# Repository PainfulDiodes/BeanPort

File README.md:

# BeanPort

Raspberry Pi Pico firmware providing a USB bridge for retrocomputers.

See also: [PainfulDiodes Blog: BeanPort](https://painfuldiodes.wordpress.com/category/beanport/)

Most homebrew retrocomputing designs provide a UART interface and use an FTDI UART-to-USB adapter to connect to a modern host computer. This means dealing with baud rates, and either fixing the CPU clock to a UART-friendly rate, or having a separate clock for the UART.

BeanPort provides an alternative solution: using a Pico, with its own USB interface, to replace the UART and FTDI adapter on the retro target.

The FTDI UM245R USB-to-parallel-FIFO module provides a similar function, but the Pico is lower cost and more readily available. It also has further potential through the Pico's SDK and additional capabilities.

The Pico's GPIOs present a two-register, 8-bit parallel interface to the target system's bus.

The Pico's USB appears as a standard CDC-ACM USB device (Abstract Control Model Communications Device Class) which the host computer recognises with a standard driver to deliver a VCP (Virtual COM Port) — on macOS: `/dev/cu.usbmodemXXXX`

USB CDC is provided by [TinyUSB](https://github.com/hathach/tinyusb) within the Pico SDK.

(By comparison, the UM245R communicates with an FTDI-specific driver on the host system, which also typically presents the device to the host as a VCP.)

Bytes flow transparently with buffering in both directions, so you can run a virtual terminal — PuTTY, screen, minicom, CoolTerm etc. — on the host computer to access the retrocomputer.

## Target Interface

BeanPort provides two 8-bit registers, distinguished by a Register Select (RS) input (which will typically be mapped to the target's A0):

| RS/A0 | Name   | Access     | Meaning                                                                                    |
|-------|--------|------------|--------------------------------------------------------------------------------------------|
| 0     | STATUS | read-only  | bit 0 = read-available, bit 1 = write-ready (matches the 6850 ACIA's RDRF/TDRE convention) |
| 1     | DATA   | read/write | write = byte to send to the host; read = byte received from the host                       |

The target will also provide EN# (enable), and R/W# - high for a read and low for a write, 6502-style. For a Z80 target: WR# would map directly to R/W#.

Reading data when none is available returns `0x00`.

## Bus Timing

The bus is handled by a PIO state machine. It responds a fixed number of PIO cycles after EN# falls - at 125MHz on an RP2040:

- **Read**: BeanPort drives the data bus as soon as EN# falls, but the byte is only valid about 90ns later for DATA, and about 145ns later for STATUS. The bus is released when EN# rises
- **Write**: BeanPort samples the data bus about 95ns after EN# falls, not when EN# rises
- RS (A0) and R/W# must be valid when EN# falls, and held until it rises

The figures above are estimated from the PIO cycle counts, and don't include level shifter delays.

Tests succeeded with:

- 10MHz Z80 - as a port-addressed device (IORQ#)
- 65C02 at up to 2.67MHz with a symmetrical clock - as a memory-mapped device, with EN# gated on PHI2

## Hardware

BeanPort should work with all current Raspberry Pi Pico variants: Pico (RP2040) and Pico 2 (RP2350), and wireless (`W`) versions. To date, it has only been tested with a non-wireless RP2040.

The following example schematic shows the designations of the Pico pins, and has 3.3V level shifters whose outputs are in spec for TTL-level inputs - 74HCT/LS logic, the W65C22N VIA and the Z80 - but I think not CMOS-level inputs such as 74HC logic. The connectors indicate how I intend to connect the BeanPort to my [Bean65](https://github.com/PainfulDiodes/bean65) board which has a W65C22N VIA "slow bus" - using the same connector layout as [Garth Wilson's 6502 design](https://wilsonminesco.com/6502primer/potpourri.html):

[kicad/beanport.pdf](kicad/beanport.pdf)

Breadboard prototype connected to a Z80 bus, with the addition of a '138 for port address decoding:

## Building and flashing

The repo's uf2 files can be transferred to Pico with standard BOOTSEL. Binary location: `build/<target>/bin/beanport.uf2`

Firmware can be built from source — see Pico documentation for build toolchain / process.

Each board gets its own build directory, e.g. `build/pico2_w/`

## License

MIT — see [LICENSE](LICENSE).

## Links

- [BeanZee](https://github.com/PainfulDiodes/BeanZee)
- [Bean65](https://github.com/PainfulDiodes/bean65)
- [BeanBoard](https://github.com/PainfulDiodes/BeanBoard)
- [PainfulDiodes Blog: BeanPort](https://painfuldiodes.wordpress.com/category/beanport/)

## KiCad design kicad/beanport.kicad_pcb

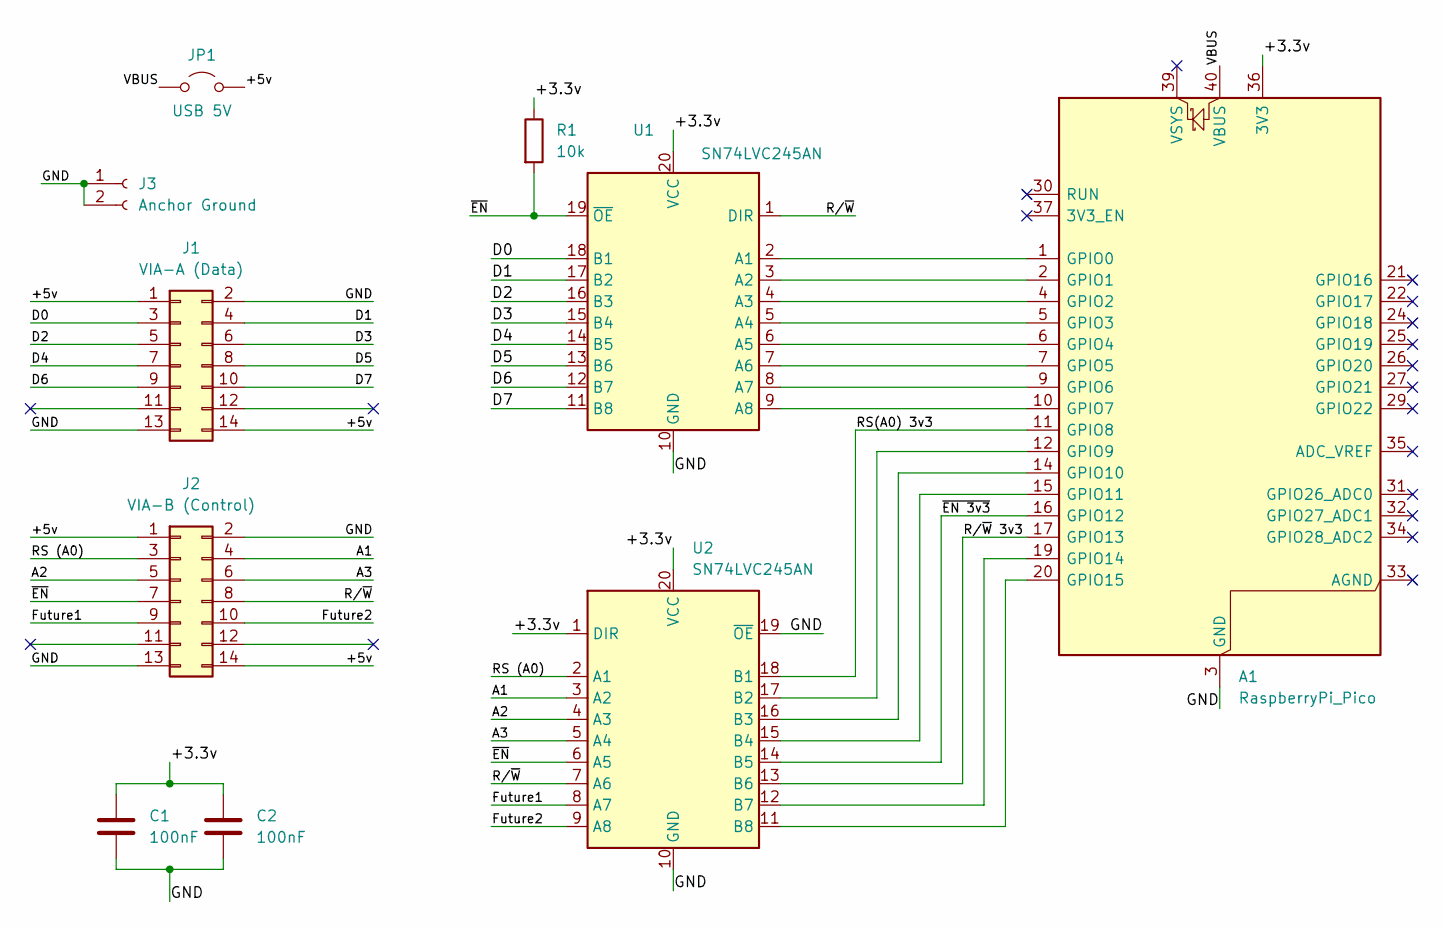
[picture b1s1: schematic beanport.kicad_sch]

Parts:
A1: RaspberryPi_Pico; RaspberryPi_Pico_Common_THT
C1, C2: 100nF; C_Disc_D5.0mm_W2.5mm_P2.50mm
J1: VIA-A (Data); PinSocket_2x07_P2.54mm_Vertical
J2: VIA-B (Control); PinSocket_2x07_P2.54mm_Vertical
J3: Anchor Ground; PinSocket_1x02_P2.54mm_Vertical
JP1: USB 5V; PinHeader_1x02_P2.54mm_Vertical
R1: 10k; R_Axial_DIN0204_L3.6mm_D1.6mm_P7.62mm_Horizontal
U1, U2: SN74LVC245AN; DIP-20_W7.62mm

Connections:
/+3.3v: A1.36 (3V3), C1.1, C2.1, R1.1, U1.20 (VCC), U2.1 (DIR), U2.20 (VCC)
/+5v: J1.1, J1.14, J2.1, J2.14, JP1.2 (B); also elsewhere on the board
/A1: J2.4, U2.3 (A2)
/A2: J2.5, U2.4 (A3)
/A3: J2.6, U2.5 (A4)
/D0: J1.3, U1.18 (B1)
/D1: J1.4, U1.17 (B2)
/D2: J1.5, U1.16 (B3)
/D3: J1.6, U1.15 (B4)
/D4: J1.7, U1.14 (B5)
/D5: J1.8, U1.13 (B6)
/D6: J1.9, U1.12 (B7)
/D7: J1.10, U1.11 (B8)
/Future1: J2.9, U2.8 (A7)
/Future2: J2.10, U2.9 (A8)
/GND: A1.3 (GND), A1.8 (GND), A1.13 (GND), A1.18 (GND), A1.23 (GND), A1.28 (GND), A1.38 (GND), C1.2, C2.2, J1.2, J1.13, J2.2, J2.13, J3.1, J3.2, U1.10 (GND), U2.10 (GND), U2.19 (~OE)
/RS (A0): J2.3, U2.2 (A1)
/RS(A0) 3v3: A1.11 (GPIO8), U2.18 (B1)
/R/~W: J2.8, U1.1 (DIR), U2.7 (A6)
/R/~W 3v3: A1.17 (GPIO13), U2.13 (B6)
/VBUS: A1.40 (VBUS), JP1.1 (A); also elsewhere on the board
/~EN 3v3: A1.16 (GPIO12), U2.14 (B5)
/~EN: J2.7, R1.2, U1.19 (~OE), U2.6 (A5)
unnamed: A1.1 (GPIO0), U1.2 (A1)
unnamed: A1.2 (GPIO1), U1.3 (A2)
unnamed: A1.4 (GPIO2), U1.4 (A3)
unnamed: A1.5 (GPIO3), U1.5 (A4)
unnamed: A1.6 (GPIO4), U1.6 (A5)
unnamed: A1.7 (GPIO5), U1.7 (A6)
unnamed: A1.9 (GPIO6), U1.8 (A7)
unnamed: A1.10 (GPIO7), U1.9 (A8)
unnamed: A1.12 (GPIO9), U2.17 (B2)
unnamed: A1.14 (GPIO10), U2.16 (B3)
unnamed: A1.15 (GPIO11), U2.15 (B4)
unnamed: A1.19 (GPIO14), U2.12 (B7)
unnamed: A1.20 (GPIO15), U2.11 (B8)

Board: 2 copper layers, 11 parts (3 on the bottom side), 36 nets, no tracks yet.

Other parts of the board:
GUIDE**: Bean65_Guide
USB 5v: JP1; PinHeader_1x02_P2.54mm_Vertical

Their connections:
/+5v: USB 5v.2 (B); also elsewhere on the board
/VBUS: USB 5v.1 (A); also elsewhere on the board
